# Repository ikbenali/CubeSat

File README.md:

# CubeSat

On this git the work done for the Project CubeSat of the Minor Robotics is found. 

Ali Ul Haq & Enes Ergyigit

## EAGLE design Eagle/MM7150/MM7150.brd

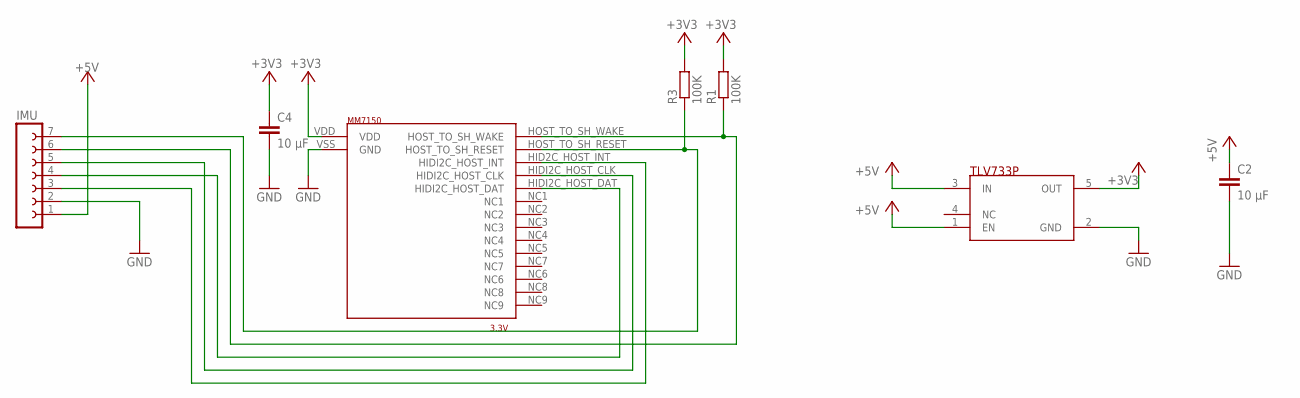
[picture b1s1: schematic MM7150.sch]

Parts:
C2, C4: 10 μF; C0805
IMU: FE07-1; FE07
R1, R3: 100K; R2012
U$1: MM7150
U$2: TLV733P; SOT23-5

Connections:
$N3: IMU.3, U$1.HID2C_HOST_INT (HIDI2C_HOST_INT)
$N4: IMU.4, U$1.HIDI2C_HOST_DAT
$N5: IMU.5, U$1.HIDI2C_HOST_CLK
+3V3: C4.1, R1.2, R3.2, U$1.VDD, U$2.5 (OUT)
+5V: C2.1, IMU.1, U$2.1 (EN), U$2.3 (IN)
GND: C2.2, C4.2, IMU.2, U$1.VSS (GND), U$2.2 (GND)
unnamed: IMU.6, R1.1, U$1.HOST_TO_SH_WAKE
unnamed: IMU.7, R3.1, U$1.HOST_TO_SH_RESET

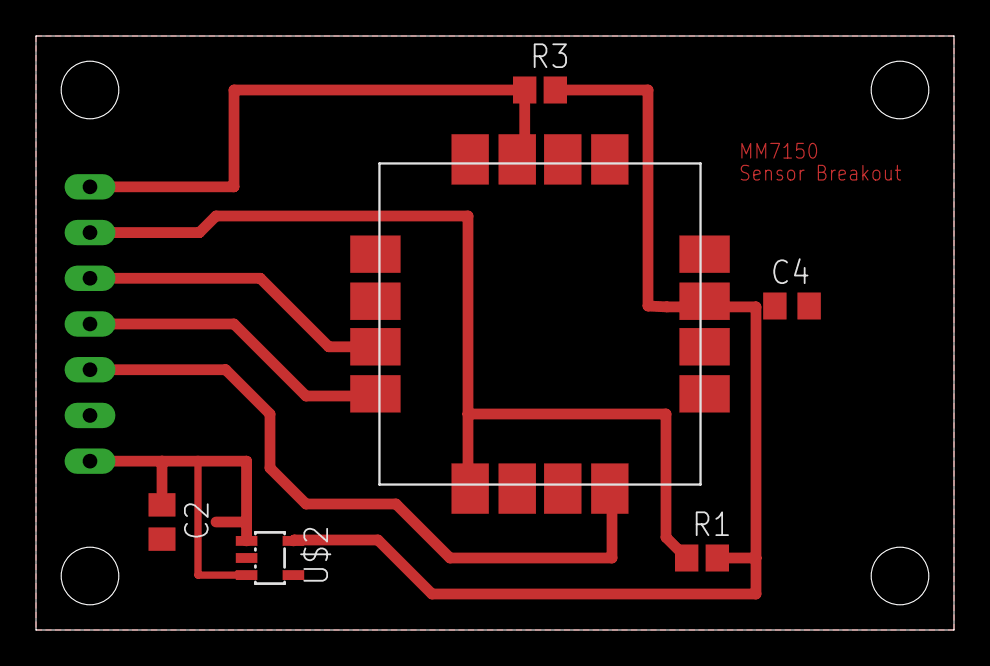
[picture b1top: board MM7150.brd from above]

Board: 2 copper layers, 51.0 x 33.0 mm, 7 parts (1 on the bottom side), 8 nets.

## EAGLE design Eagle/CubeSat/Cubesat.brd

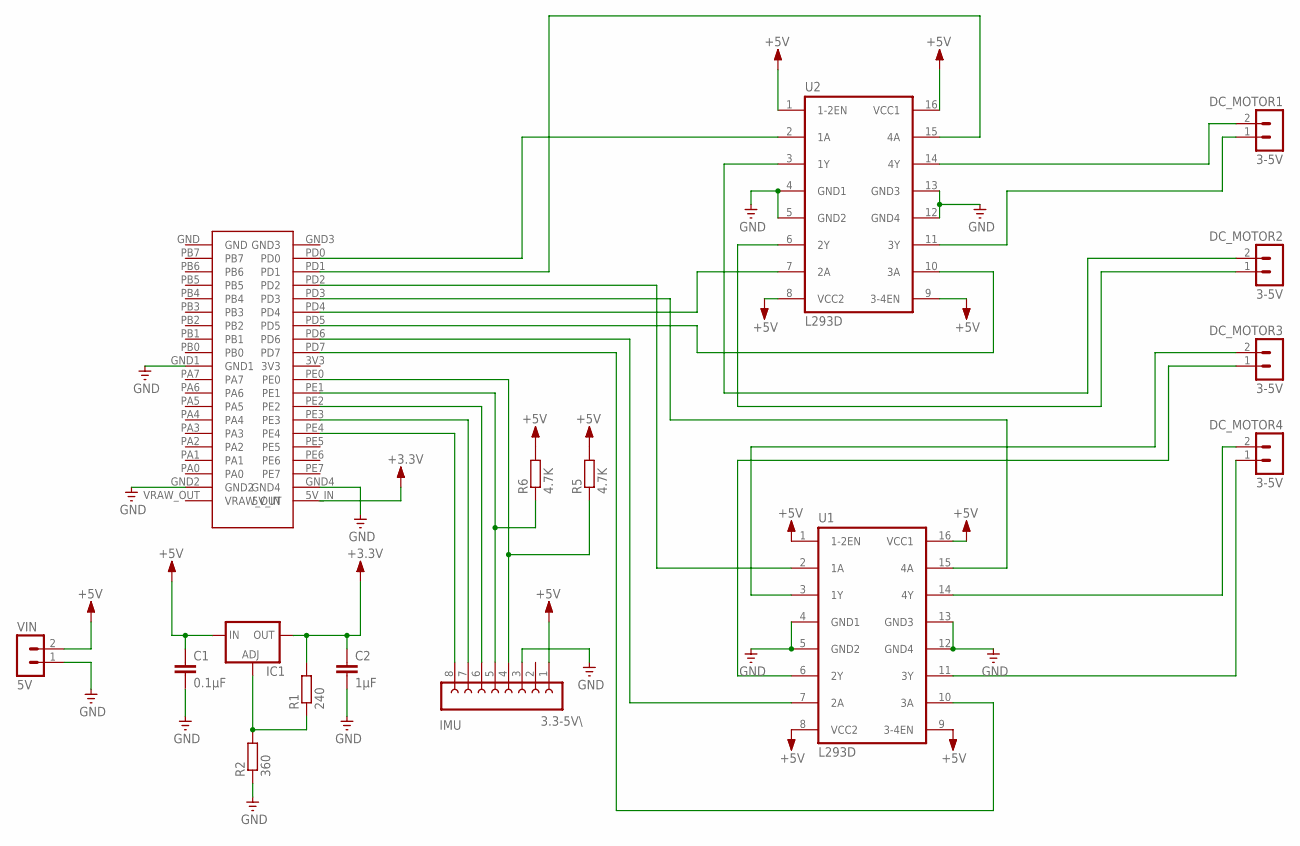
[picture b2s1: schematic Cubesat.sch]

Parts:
C1: 0.1μF; C1210
C2: 1μF; C1210
DC_MOTOR1, DC_MOTOR2, DC_MOTOR3, DC_MOTOR4: 3-5V; MA02-1Y
IC1: LM317TS; 317TS
IMU: 3.3-5V\; FE08-1
R1: 240; M2012
R2: 360; M2012
R5, R6: 4.7K; M2012
U1, U2: L293D; DIL16
VIN: 5V; MA02-1Y
XMEGA256A3U: ATXMEGA256A3U

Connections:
+5V: C1.1, C2.1, IC1.2 (OUT), IC1.3 (IN), IMU.1, R1.2, R5.2, R6.2, U1.1 (1-2EN), U1.8 (VCC2), U1.9 (3-4EN), U1.16 (VCC1), U2.1 (1-2EN), U2.8 (VCC2), U2.9 (3-4EN), U2.16 (VCC1), VIN.2, XMEGA256A3U.5V_IN
GND: C1.2, C2.2, IMU.3, R2.1, U1.4 (GND1), U1.5 (GND2), U1.12 (GND4), U1.13 (GND3), U2.4 (GND1), U2.5 (GND2), U2.12 (GND4), U2.13 (GND3), VIN.1, XMEGA256A3U.GND1, XMEGA256A3U.GND2, XMEGA256A3U.GND4
unnamed: DC_MOTOR1.2, U2.14 (4Y)
unnamed: DC_MOTOR1.1, U2.11 (3Y)
unnamed: U2.2 (1A), XMEGA256A3U.PD0
unnamed: U1.2 (1A), XMEGA256A3U.PD2
unnamed: IMU.4, R5.1, XMEGA256A3U.PE0
unnamed: IMU.5, R6.1, XMEGA256A3U.PE1
unnamed: DC_MOTOR2.2, U2.3 (1Y)
unnamed: DC_MOTOR2.1, U2.6 (2Y)
unnamed: IMU.6, XMEGA256A3U.PE2
unnamed: DC_MOTOR3.1, U1.6 (2Y)
unnamed: U1.15 (4A), XMEGA256A3U.PD3
unnamed: U2.7 (2A), XMEGA256A3U.PD4
unnamed: IMU.7, XMEGA256A3U.PE3
unnamed: DC_MOTOR4.2, U1.14 (4Y)
unnamed: DC_MOTOR3.2, U1.3 (1Y)
unnamed: DC_MOTOR4.1, U1.11 (3Y)
unnamed: U1.10 (3A), XMEGA256A3U.PD7
unnamed: IMU.8, XMEGA256A3U.PE4
unnamed: U2.15 (4A), XMEGA256A3U.PD1
unnamed: U1.7 (2A), XMEGA256A3U.PD6
unnamed: U2.10 (3A), XMEGA256A3U.PD5
unnamed: IC1.1 (ADJ), R1.1, R2.2

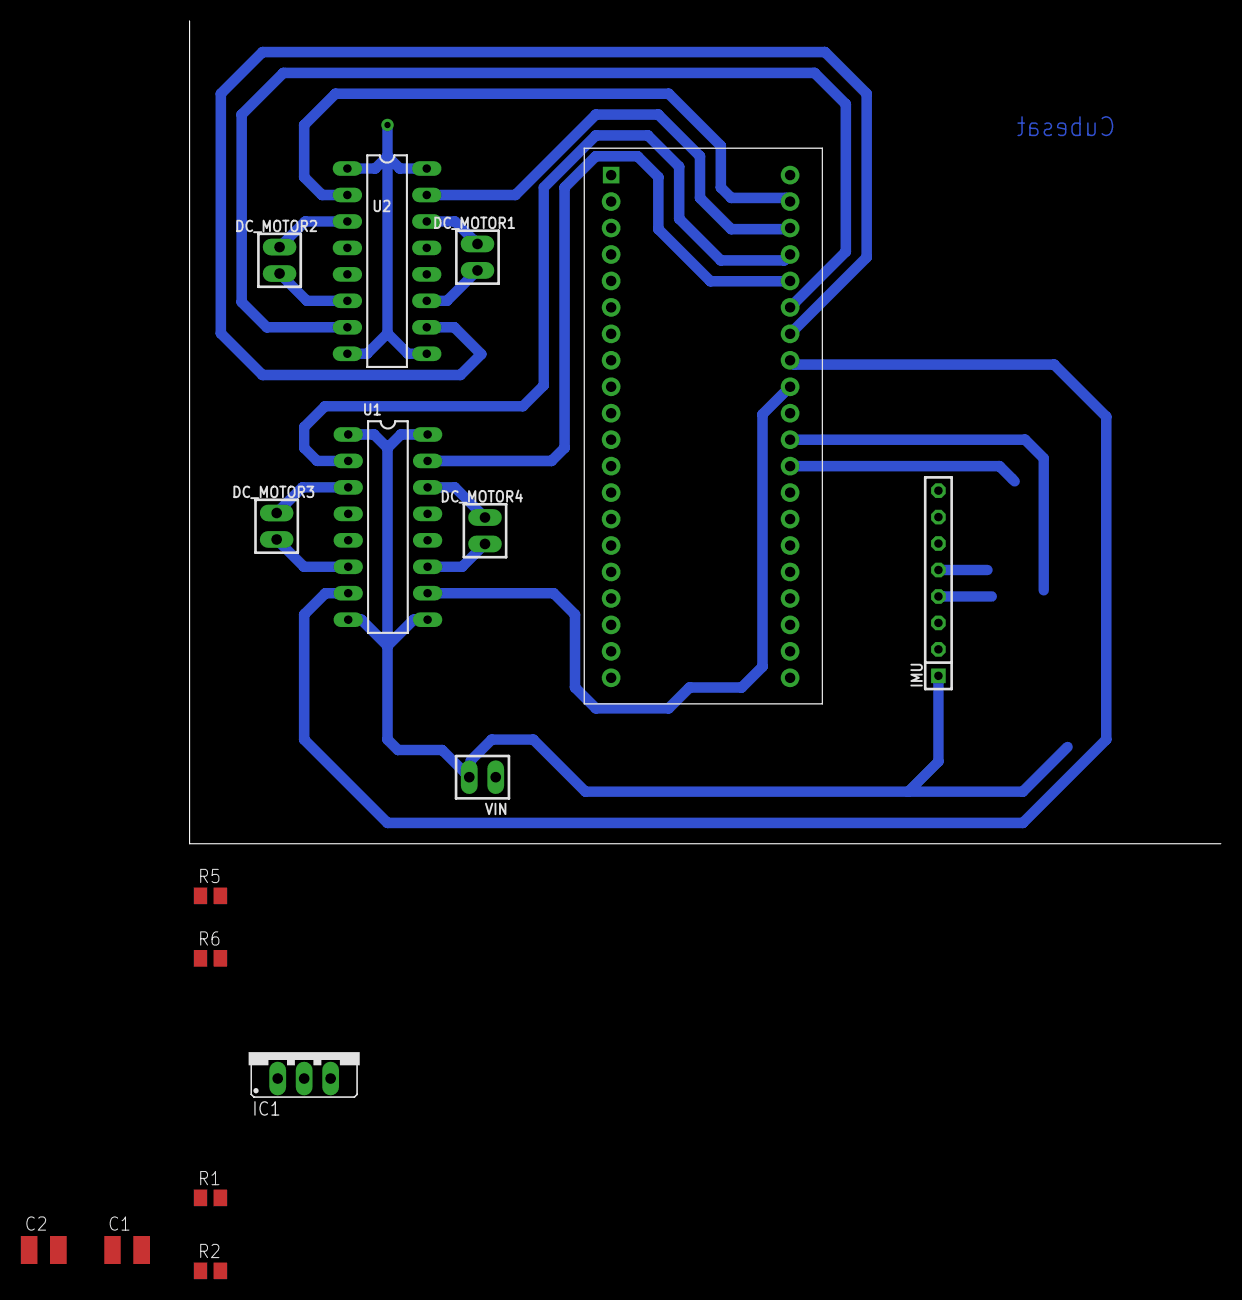
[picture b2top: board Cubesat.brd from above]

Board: 2 copper layers, 16 parts (0 on the bottom side), 24 nets.

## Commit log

2017-02-13 videos
2017-02-13 update names
2017-02-13 comitt

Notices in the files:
parts and their libraries:
supply1: Copyright (C) 2007, Bob Starr
